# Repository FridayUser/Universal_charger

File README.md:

View this project on [CADLAB.io](https://cadlab.io/project/28066). 

# Witam w projekcie ładowarki!

# Update plików
**Proszę o pisanie jasnego podsumowania i zwięzłych opisów** przy zatwierdzaniu plików. W szczególności plików innych niż programy. Pamietajcie, że po zatwierdzeniu należy też pliki przesłać. ewentualnie dodać jakieś nowe. Jeśli ktoś nie ogarnia gita to polecam wersję desktop.
## Tworzenie plików i folderów
Starajmy się twożyć jak najbardziej przejrzyście to repozytorium, żeby się poprostu nie zgubić w tym wszystkim

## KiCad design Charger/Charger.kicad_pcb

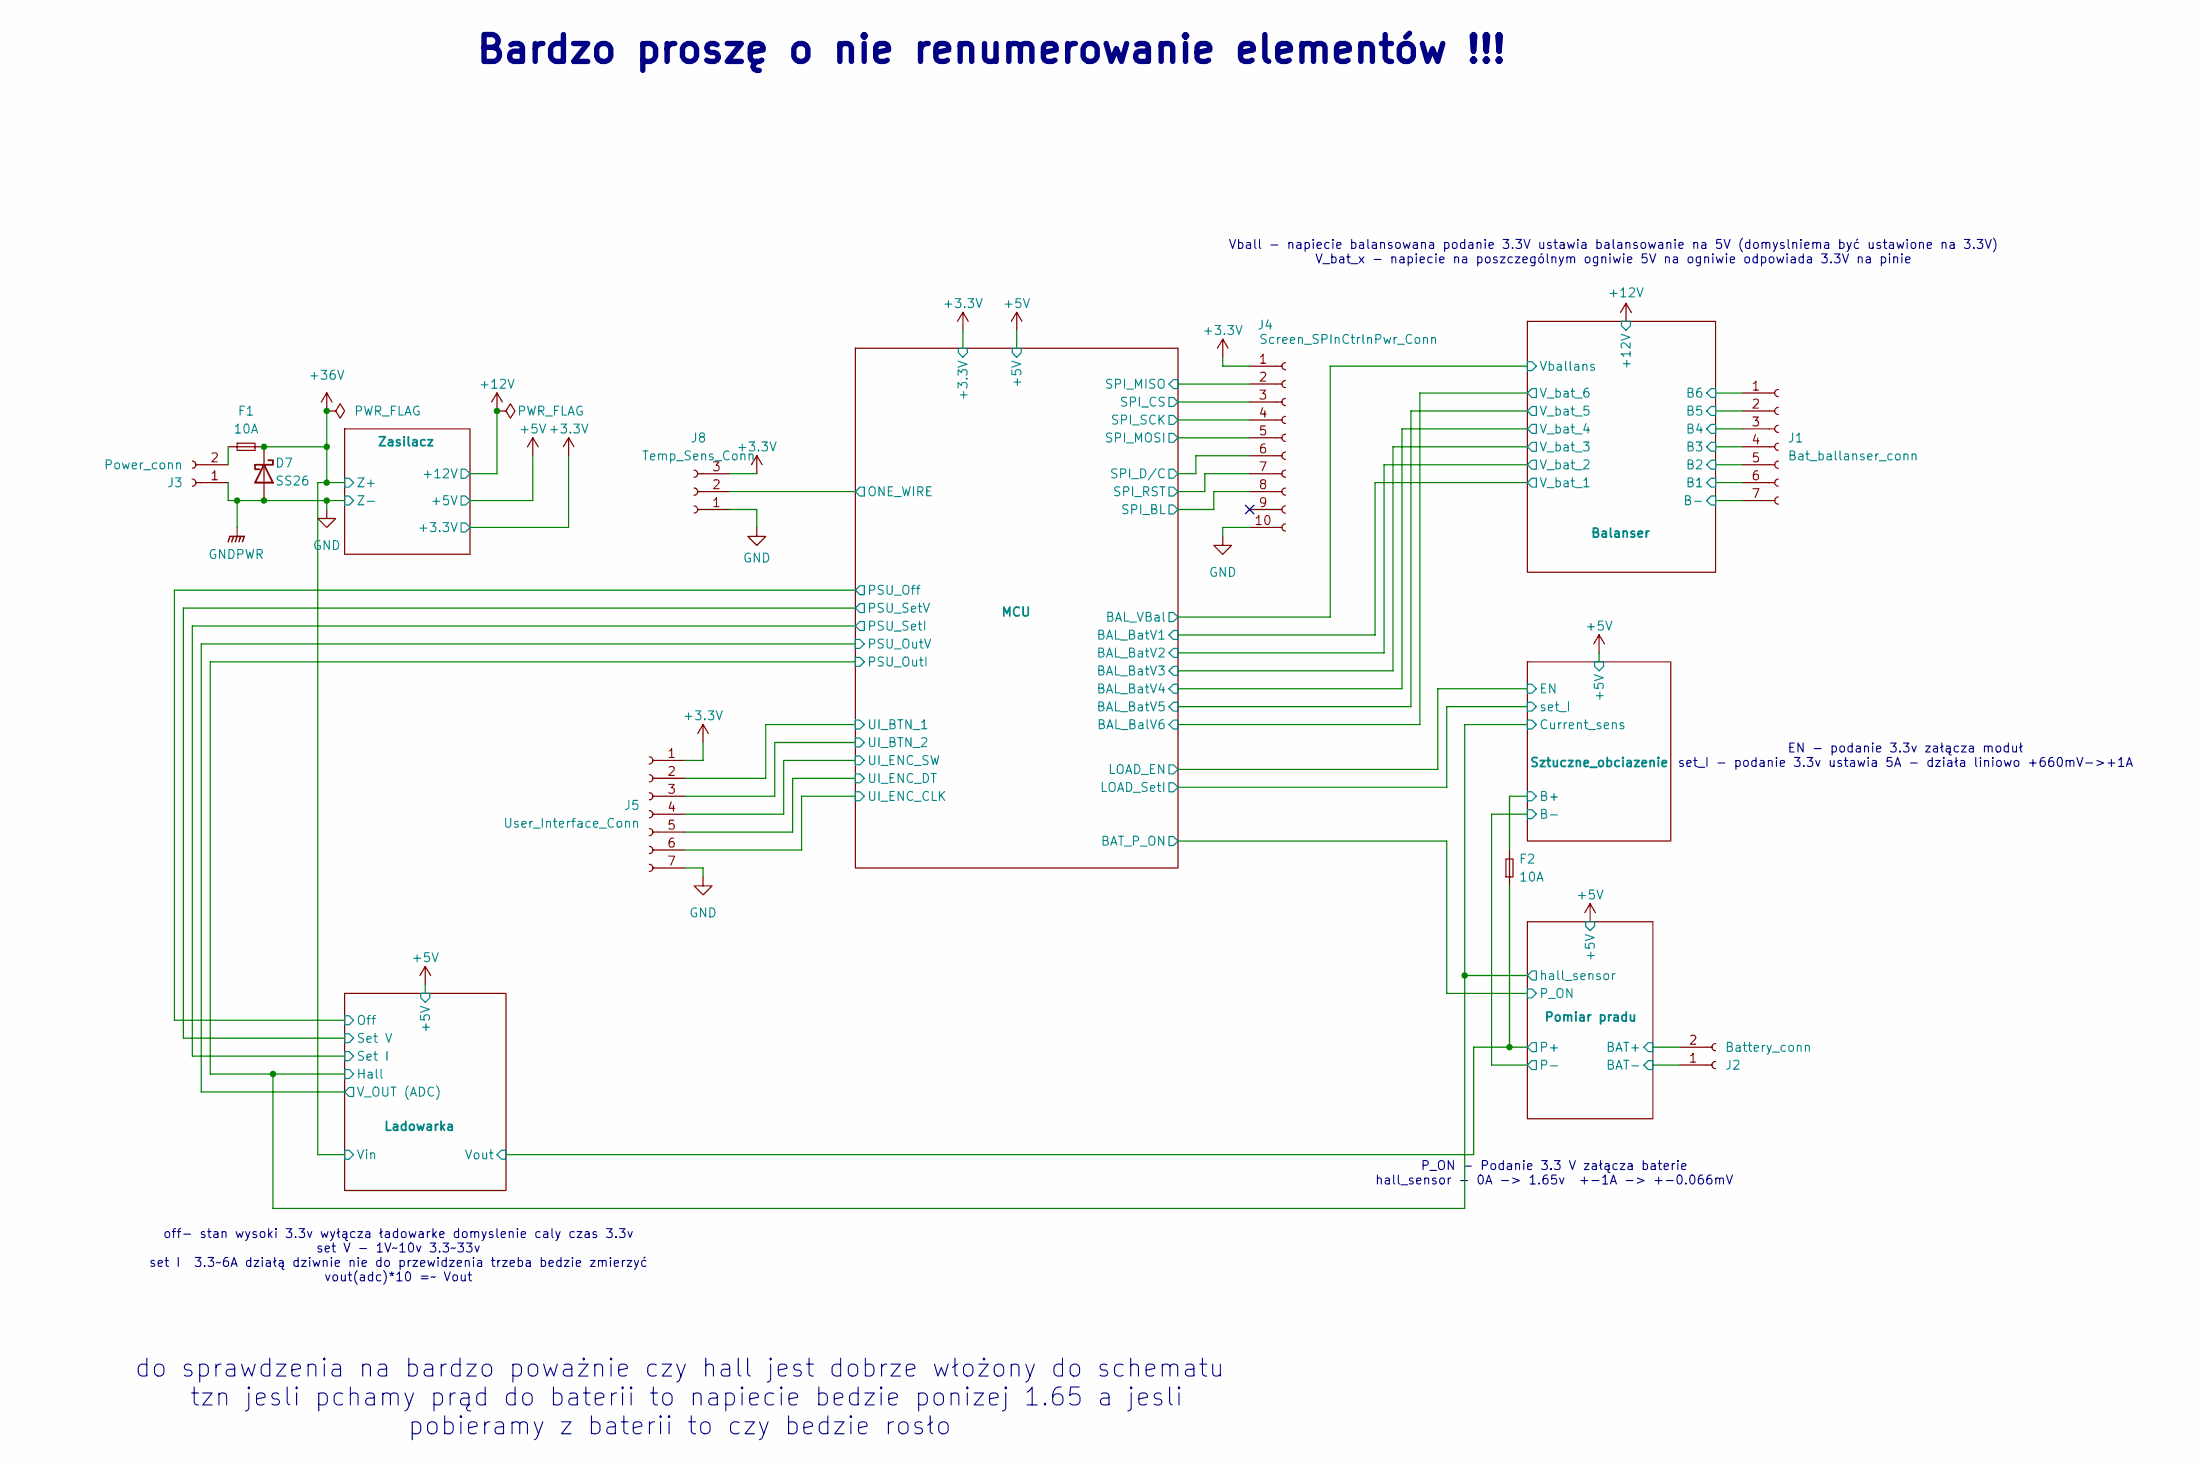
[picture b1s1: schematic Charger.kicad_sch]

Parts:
D7: SS26; D_SMA
F1, F2: 10A; Fuse_2010_5025Metric_Pad1.52x2.65mm_HandSolder
J1: Bat_ballanser_conn; PinHeader_1x07_P2.54mm_Horizontal
J2: Battery_conn; AMASS_XT60PW-M_1x02_P7.20mm_Horizontal
J3: Power_conn; AMASS_XT60PW-M_1x02_P7.20mm_Horizontal
J4: Screen_SPInCtrlnPwr_Conn; PinHeader_1x10_P2.54mm_Vertical
J5: User_Interface_Conn; PinHeader_1x07_P2.54mm_Vertical
J8: Temp_Sens_Conn; PinHeader_1x03_P2.54mm_Vertical

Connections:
+3.3V: J4.1, J5.1, J8.3; also elsewhere on the board
+36V: D7.1 (K), F1.2; also elsewhere on the board
/Balanser/B1: J1.6; also elsewhere on the board
/Balanser/B2: J1.5; also elsewhere on the board
/Balanser/B3: J1.4; also elsewhere on the board
/Balanser/B4: J1.3; also elsewhere on the board
/Balanser/B5: J1.2; also elsewhere on the board
/Balanser/B6: J1.1; also elsewhere on the board
/Ladowarka/Vout: F2.1; also elsewhere on the board
/Pomiar pradu/BAT+: J2.2; also elsewhere on the board
/Pomiar pradu/BAT-: J2.1; also elsewhere on the board
/Sztuczne_obciazenie/B+: F2.2; also elsewhere on the board
GND: D7.2 (A), J1.7, J3.1, J4.10, J5.7, J8.1; also elsewhere on the board
GPIO4: J8.2; also elsewhere on the board
GPIO11: J5.6; also elsewhere on the board
GPIO12: J5.5; also elsewhere on the board
GPIO13: J5.4; also elsewhere on the board
GPIO14: J5.3; also elsewhere on the board
GPIO15: J5.2; also elsewhere on the board
GPIO16: J4.2; also elsewhere on the board
GPIO17: J4.3; also elsewhere on the board
GPIO18: J4.4; also elsewhere on the board
GPIO19: J4.5; also elsewhere on the board
GPIO20: J4.6; also elsewhere on the board
GPIO21: J4.7; also elsewhere on the board
GPIO22: J4.8; also elsewhere on the board
unnamed: F1.1, J3.2

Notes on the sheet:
EN - podanie 3.3v załącza moduł set_I - podanie 3.3v ustawia 5A - działa liniowo +660mV->+1A
off- stan wysoki 3.3v wyłącza ładowarke domyslenie caly czas 3.3v set V - 1V~10v 3.3~33v set I 3.3~6A działą dziwnie nie do przewidzenia trzeba bedzie zmierzyć vout(adc)*10 =~ Vout
Bardzo proszę o nie renumerowanie elementów !!!
Vball - napiecie balansowana podanie 3.3V ustawia balansowanie na 5V (domyslniema być ustawione na 3.3V) V_bat_x - napiecie na poszczególnym ogniwie 5V na ogniwie odpowiada 3.3V na pinie
do sprawdzenia na bardzo poważnie czy hall jest dobrze włożony do schematu tzn jesli pchamy prąd do baterii to napiecie bedzie ponizej 1.65 a jesli pobieramy z baterii to czy bedzie rosło
P_ON - Podanie 3.3 V załącza baterie hall_sensor - 0A -> 1.65v +-1A -> +-0.066mV

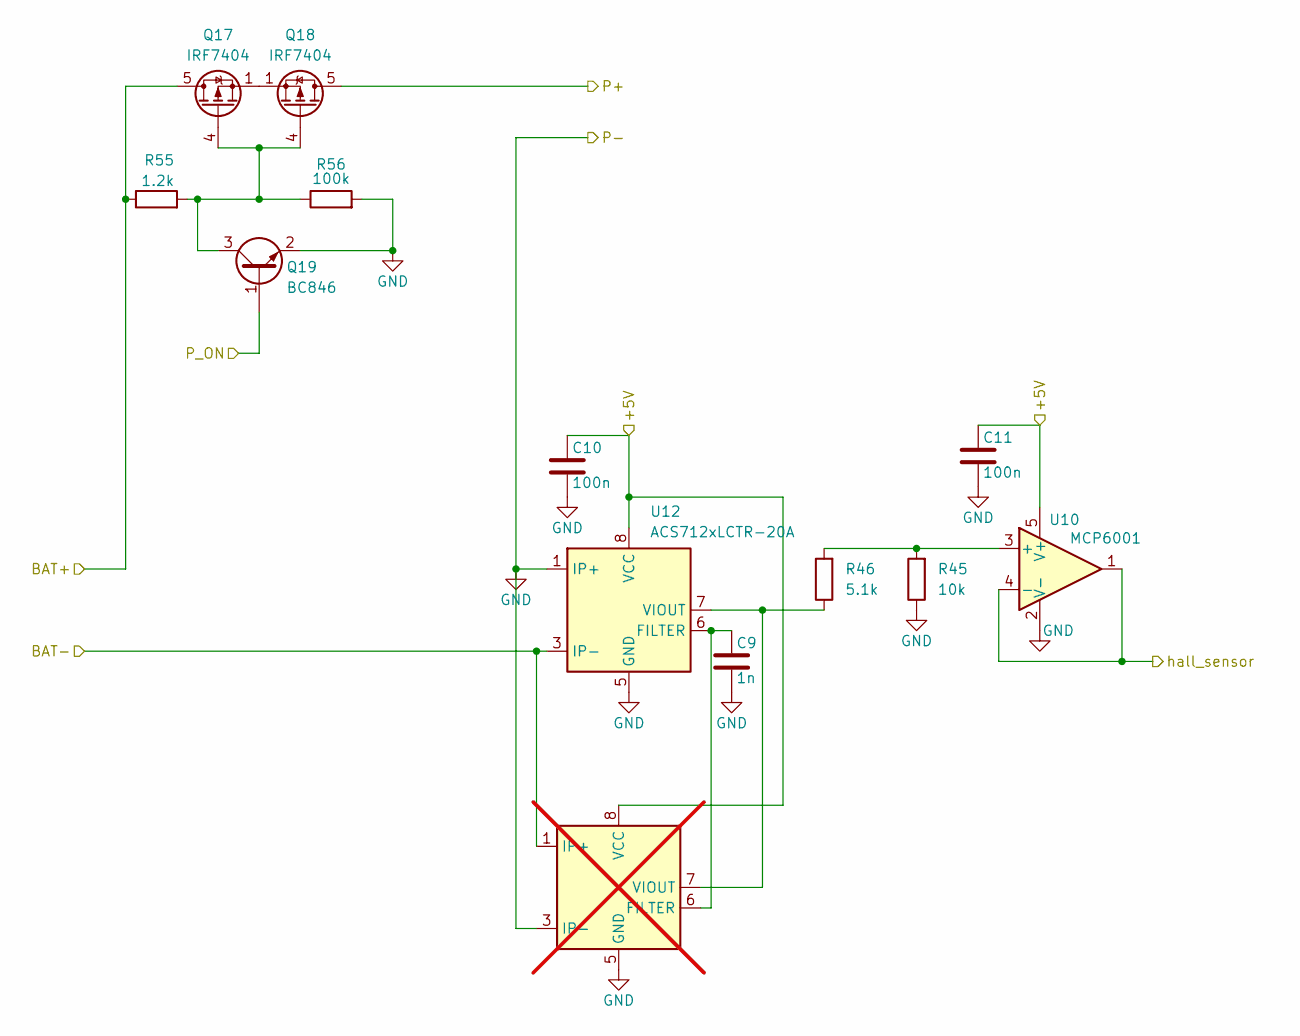
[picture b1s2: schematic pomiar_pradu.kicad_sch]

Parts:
C9: 1n; C_0805_2012Metric_Pad1.18x1.45mm_HandSolder
C10, C11: 100n; C_0805_2012Metric_Pad1.18x1.45mm_HandSolder
Q17, Q18: IRF7404; SOIC-8_3.9x4.9mm_P1.27mm
Q19: BC846; SOT-323_SC-70
R45: 10k; R_0805_2012Metric_Pad1.20x1.40mm_HandSolder
R46: 5.1k; R_0805_2012Metric_Pad1.20x1.40mm_HandSolder
R55: 1.2k; R_0805_2012Metric_Pad1.20x1.40mm_HandSolder
R56: 100k; R_0805_2012Metric_Pad1.20x1.40mm_HandSolder
U7: ACS712xLCTR-20A; SOIC-8_3.9x4.9mm_P1.27mm; not fitted
U10: MCP6001; SOT-23-5
U12: ACS712xLCTR-20A; SOIC-8_3.9x4.9mm_P1.27mm

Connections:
+5V: C10.1, C11.1, U7.8 (VCC), U10.5 (V+), U12.8 (VCC); also elsewhere on the board
/Ladowarka/Hall: U10.1, U10.4 (-); also elsewhere on the board
/Ladowarka/Vout: Q18.5 (D), Q18.6 (D), Q18.7 (D), Q18.8 (D); also elsewhere on the board
/Pomiar pradu/BAT+: Q17.5 (D), Q17.6 (D), Q17.7 (D), Q17.8 (D), R55.1; also elsewhere on the board
/Pomiar pradu/BAT-: U7.1 (IP+), U7.2 (IP+), U12.3 (IP-), U12.4 (IP-); also elsewhere on the board
GND: C9.2, C10.2, C11.2, Q19.2 (E), R45.1, R56.2, U7.3 (IP-), U7.4 (IP-), U7.5 (GND), U10.2 (V-), U12.1 (IP+), U12.2 (IP+), U12.5 (GND); also elsewhere on the board
GPIO10: Q19.1 (B); also elsewhere on the board
unnamed: Q17.4 (G), Q18.4 (G), Q19.3 (C), R55.2, R56.1
unnamed: Q17.1 (S), Q17.2 (S), Q17.3 (S), Q18.1 (S), Q18.2 (S), Q18.3 (S)
unnamed: R45.2, R46.2, U10.3 (+)
unnamed: C9.1, U7.6 (FILTER), U12.6 (FILTER)
unnamed 106: R46.1, U7.7 (VIOUT), U12.7 (VIOUT); also elsewhere on the board

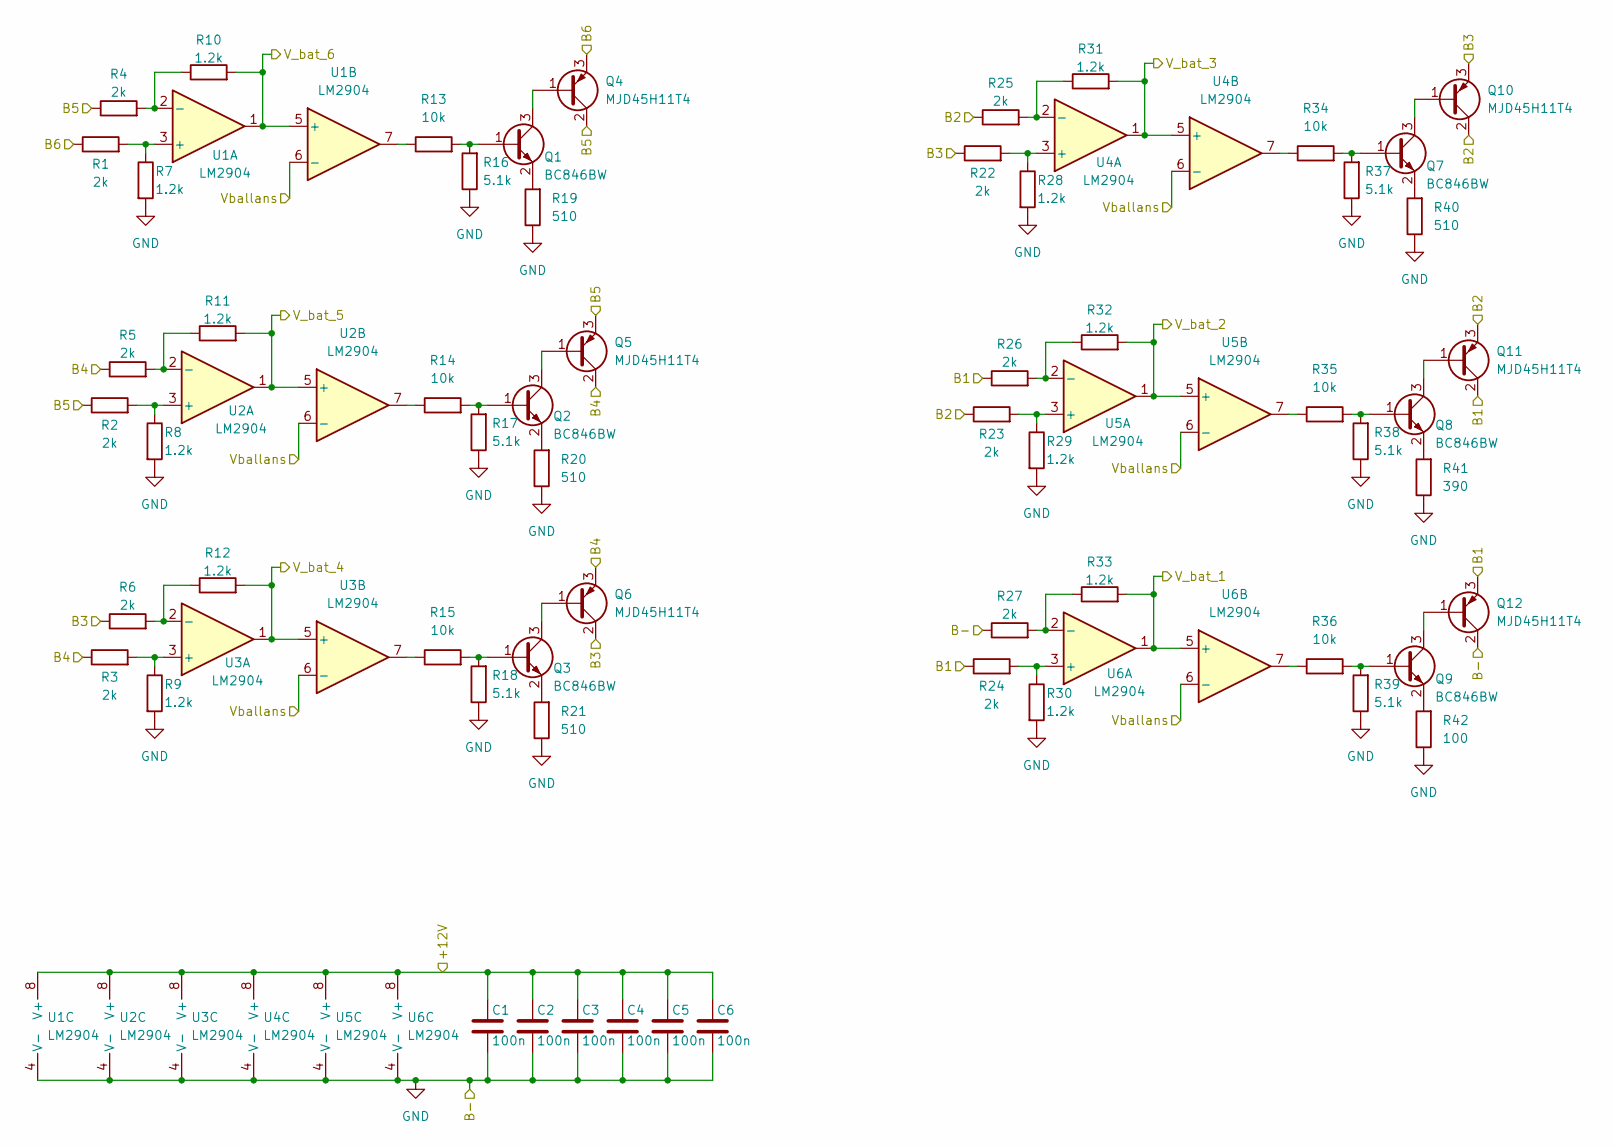
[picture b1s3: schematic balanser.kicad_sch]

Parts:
C1, C2, C3, C4, C5, C6: 100n; C_0805_2012Metric_Pad1.18x1.45mm_HandSolder
Q1, Q2, Q3, Q7, Q8, Q9: BC846BW; SOT-323_SC-70
Q4, Q5, Q6, Q10, Q11, Q12: MJD45H11T4; TO-252-2
R1, R2, R3, R4, R5, R6, R22, R23, R24, R25, R26, R27: 2k; R_0805_2012Metric_Pad1.20x1.40mm_HandSolder
R7, R8, R9, R10, R11, R12, R28, R29, R30, R31, R32, R33: 1.2k; R_0805_2012Metric_Pad1.20x1.40mm_HandSolder
R13, R14, R15, R34, R35, R36: 10k; R_0805_2012Metric_Pad1.20x1.40mm_HandSolder
R16, R17, R18, R37, R38, R39: 5.1k; R_0805_2012Metric_Pad1.20x1.40mm_HandSolder
R19, R20, R21, R40: 510; R_0805_2012Metric_Pad1.20x1.40mm_HandSolder
R41: 390; R_0805_2012Metric_Pad1.20x1.40mm_HandSolder
R42: 100; R_0805_2012Metric_Pad1.20x1.40mm_HandSolder
U1, U2, U3, U4, U5, U6: LM2904; SO-8_3.9x4.9mm_P1.27mm

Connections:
+12V: C1.1, C2.1, C3.1, C4.1, C5.1, C6.1, U1.8 (V+), U2.8 (V+), U3.8 (V+), U4.8 (V+), U5.8 (V+), U6.8 (V+); also elsewhere on the board
/Balanser/B1: Q11.2 (C), Q12.3 (E), R24.1, R26.1; also elsewhere on the board
/Balanser/B2: Q10.2 (C), Q11.3 (E), R23.1, R25.1; also elsewhere on the board
/Balanser/B3: Q6.2 (C), Q10.3 (E), R6.1, R22.1; also elsewhere on the board
/Balanser/B4: Q5.2 (C), Q6.3 (E), R3.1, R5.1; also elsewhere on the board
/Balanser/B5: Q4.2 (C), Q5.3 (E), R2.1, R4.1; also elsewhere on the board
/Balanser/B6: Q4.3 (E), R1.1; also elsewhere on the board
/Balanser/V_bat_1: R33.2, U6.1, U6.5 (+); also elsewhere on the board
/Balanser/V_bat_2: R32.2, U5.1, U5.5 (+); also elsewhere on the board
/Balanser/V_bat_3: R31.2, U4.1, U4.5 (+); also elsewhere on the board
/Balanser/V_bat_4: R12.2, U3.1, U3.5 (+); also elsewhere on the board
/Balanser/V_bat_5: R11.2, U2.1, U2.5 (+); also elsewhere on the board
/Balanser/V_bat_6: R10.2, U1.1, U1.5 (+); also elsewhere on the board
/Balanser/Vballans: U1.6 (-), U2.6 (-), U3.6 (-), U4.6 (-), U5.6 (-), U6.6 (-); also elsewhere on the board
GND: C1.2, C2.2, C3.2, C4.2, C5.2, C6.2, Q12.2 (C), R7.2, R8.2, R9.2, R16.1, R17.1, R18.1, R19.1, R20.1, R21.1, R27.1, R28.2, R29.2, R30.2, R37.1, R38.1, R39.1, R40.1, R41.1, R42.1, U1.4 (V-), U2.4 (V-), U3.4 (V-), U4.4 (V-), U5.4 (V-), U6.4 (V-); also elsewhere on the board
unnamed: Q1.1 (B), R13.2, R16.2
unnamed: Q1.3 (C), Q4.1 (B)
unnamed: Q1.2 (E), R19.2
unnamed: Q2.1 (B), R14.2, R17.2
unnamed: Q2.3 (C), Q5.1 (B)
unnamed: Q2.2 (E), R20.2
unnamed: Q3.1 (B), R15.2, R18.2
unnamed: Q3.3 (C), Q6.1 (B)
unnamed: Q3.2 (E), R21.2
unnamed: Q7.1 (B), R34.2, R37.2
unnamed: Q7.2 (E), R40.2
unnamed: Q8.1 (B), R35.2, R38.2
unnamed: Q8.2 (E), R41.2
unnamed: Q9.1 (B), R36.2, R39.2
unnamed: Q9.2 (E), R42.2
unnamed: Q7.3 (C), Q10.1 (B)
unnamed: Q8.3 (C), Q11.1 (B)
unnamed: Q9.3 (C), Q12.1 (B)
unnamed: R13.1, U1.7
unnamed: R14.1, U2.7
unnamed: R15.1, U3.7
unnamed: R34.1, U4.7
unnamed: R35.1, U5.7
unnamed: R36.1, U6.7
unnamed: R1.2, R7.1, U1.3 (+)
unnamed: R4.2, R10.1, U1.2 (-)
unnamed: R2.2, R8.1, U2.3 (+)
unnamed: R5.2, R11.1, U2.2 (-)
unnamed: R3.2, R9.1, U3.3 (+)
unnamed: R6.2, R12.1, U3.2 (-)
unnamed: R22.2, R28.1, U4.3 (+)
unnamed: R25.2, R31.1, U4.2 (-)
unnamed: R23.2, R29.1, U5.3 (+)
unnamed: R26.2, R32.1, U5.2 (-)
unnamed: R24.2, R30.1, U6.3 (+)
unnamed: R27.2, R33.1, U6.2 (-)

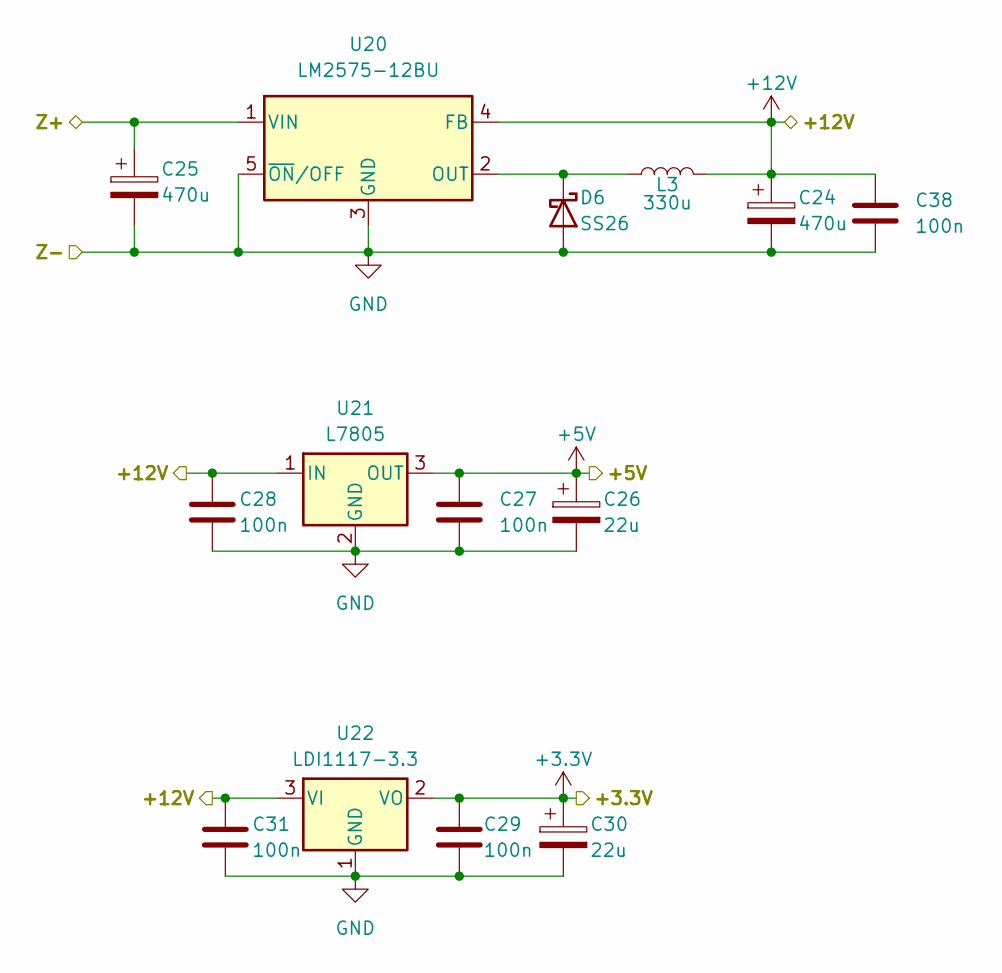
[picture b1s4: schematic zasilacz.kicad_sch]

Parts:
C24, C25: 470u; CP_Elec_12.5x13.5
C26, C30: 22u; CP_Elec_4x5.4
C27, C28, C29, C31, C38: 100n; C_0805_2012Metric_Pad1.18x1.45mm_HandSolder
D6: SS26; D_SMA
L3: 330u; L_Bourns_SRR1208_12.7x12.7mm
U20: LM2575-12BU; TO-263-5_TabPin3
U21: L7805; TO-263-2
U22: LDI1117-3.3; SOT-223-3_TabPin2

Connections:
+3.3V: C29.1, C30.1, U22.2 (VO); also elsewhere on the board
+5V: C26.1, C27.1, U21.3 (OUT); also elsewhere on the board
+12V: C24.1, C28.1, C31.1, C38.1, L3.2, U20.4 (FB), U21.1 (IN), U22.3 (VI); also elsewhere on the board
+36V: C25.1, U20.1 (VIN); also elsewhere on the board
GND: C24.2, C25.2, C26.2, C27.2, C28.2, C29.2, C30.2, C31.2, C38.2, D6.2 (A), U20.3 (GND), U20.5 (~ON/OFF), U21.2 (GND), U22.1 (GND); also elsewhere on the board
unnamed: D6.1 (K), L3.1, U20.2 (OUT)

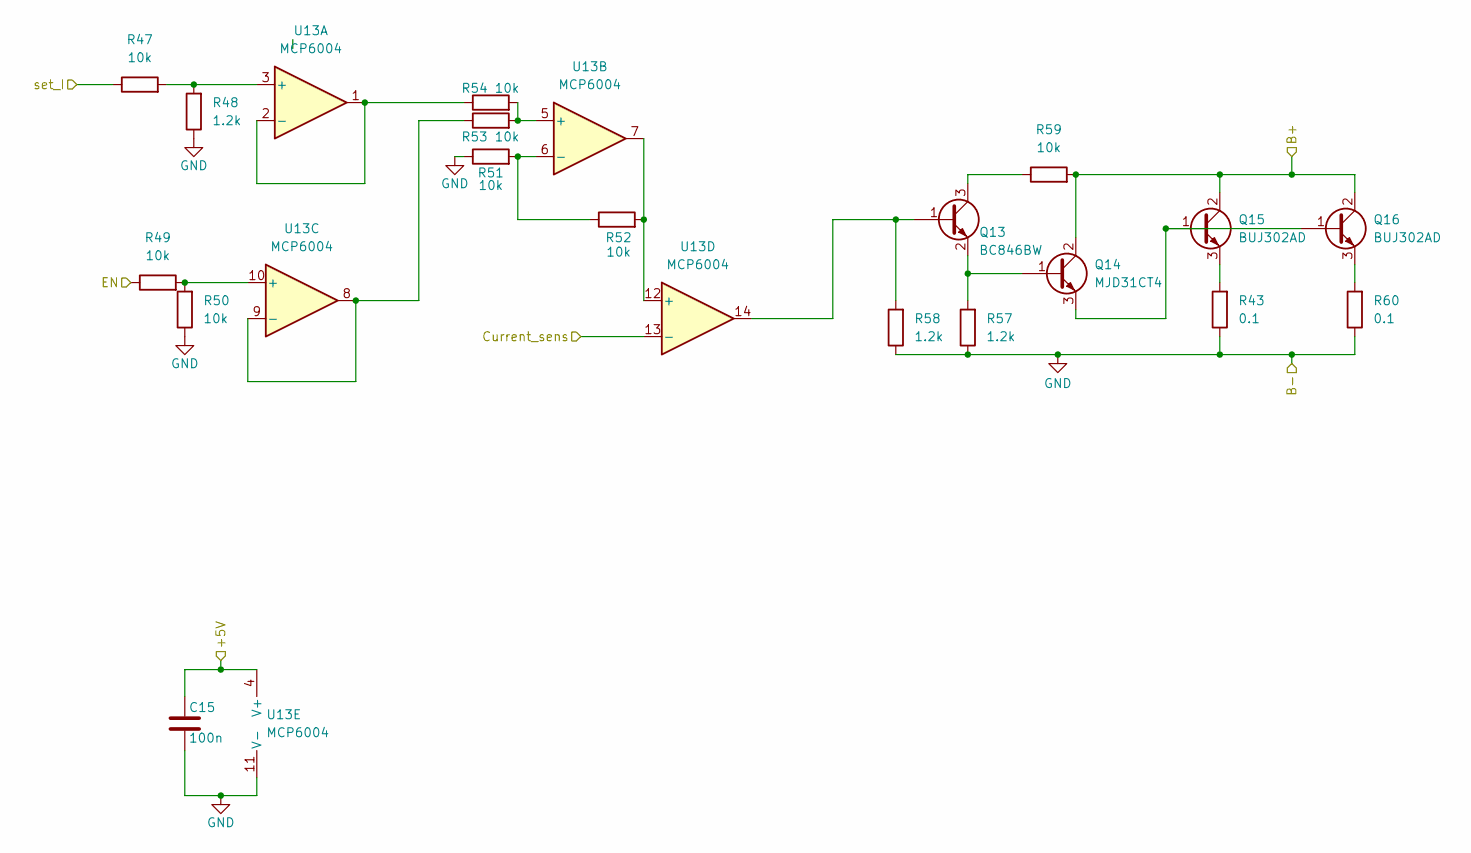
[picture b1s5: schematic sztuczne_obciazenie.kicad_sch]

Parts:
C15: 100n; C_0805_2012Metric_Pad1.18x1.45mm_HandSolder
Q13: BC846BW; SOT-323_SC-70
Q14: MJD31CT4; TO-252-2
Q15, Q16: BUJ302AD; TO-252-2
R43, R60: 0.1; R_1206_3216Metric_Pad1.30x1.75mm_HandSolder
R47, R49, R50, R51, R52, R53, R54, R59: 10k; R_0805_2012Metric_Pad1.20x1.40mm_HandSolder
R48, R57, R58: 1.2k; R_0805_2012Metric_Pad1.20x1.40mm_HandSolder
U13: MCP6004; SOIC-14_3.9x8.7mm_P1.27mm

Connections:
+5V: C15.1, U13.4 (V+); also elsewhere on the board
/Ladowarka/Hall: U13.13 (-); also elsewhere on the board
/MCU/LOAD_SetI: R47.1; also elsewhere on the board
/Sztuczne_obciazenie/B+: Q14.2 (C), Q15.2 (C), Q16.2 (C), R59.2; also elsewhere on the board
GND: C15.2, R43.1, R48.1, R50.1, R51.1, R57.1, R58.1, R60.1, U13.11 (V-); also elsewhere on the board
GPIO8: R49.1; also elsewhere on the board
unnamed: Q13.1 (B), R58.2, U13.14
unnamed: Q13.3 (C), R59.1
unnamed: Q13.2 (E), Q14.1 (B), R57.2
unnamed: Q14.3 (E), Q15.1 (B), Q16.1 (B)
unnamed: Q15.3 (E), R43.2
unnamed: Q16.3 (E), R60.2
unnamed: R47.2, R48.2, U13.3 (+)
unnamed: R54.1, U13.1, U13.2 (-)
unnamed: R53.2, R54.2, U13.5 (+)
unnamed: R51.2, R52.1, U13.6 (-)
unnamed: R49.2, R50.2, U13.10 (+)
unnamed: R53.1, U13.8, U13.9 (-)
unnamed: R52.2, U13.7, U13.12 (+)

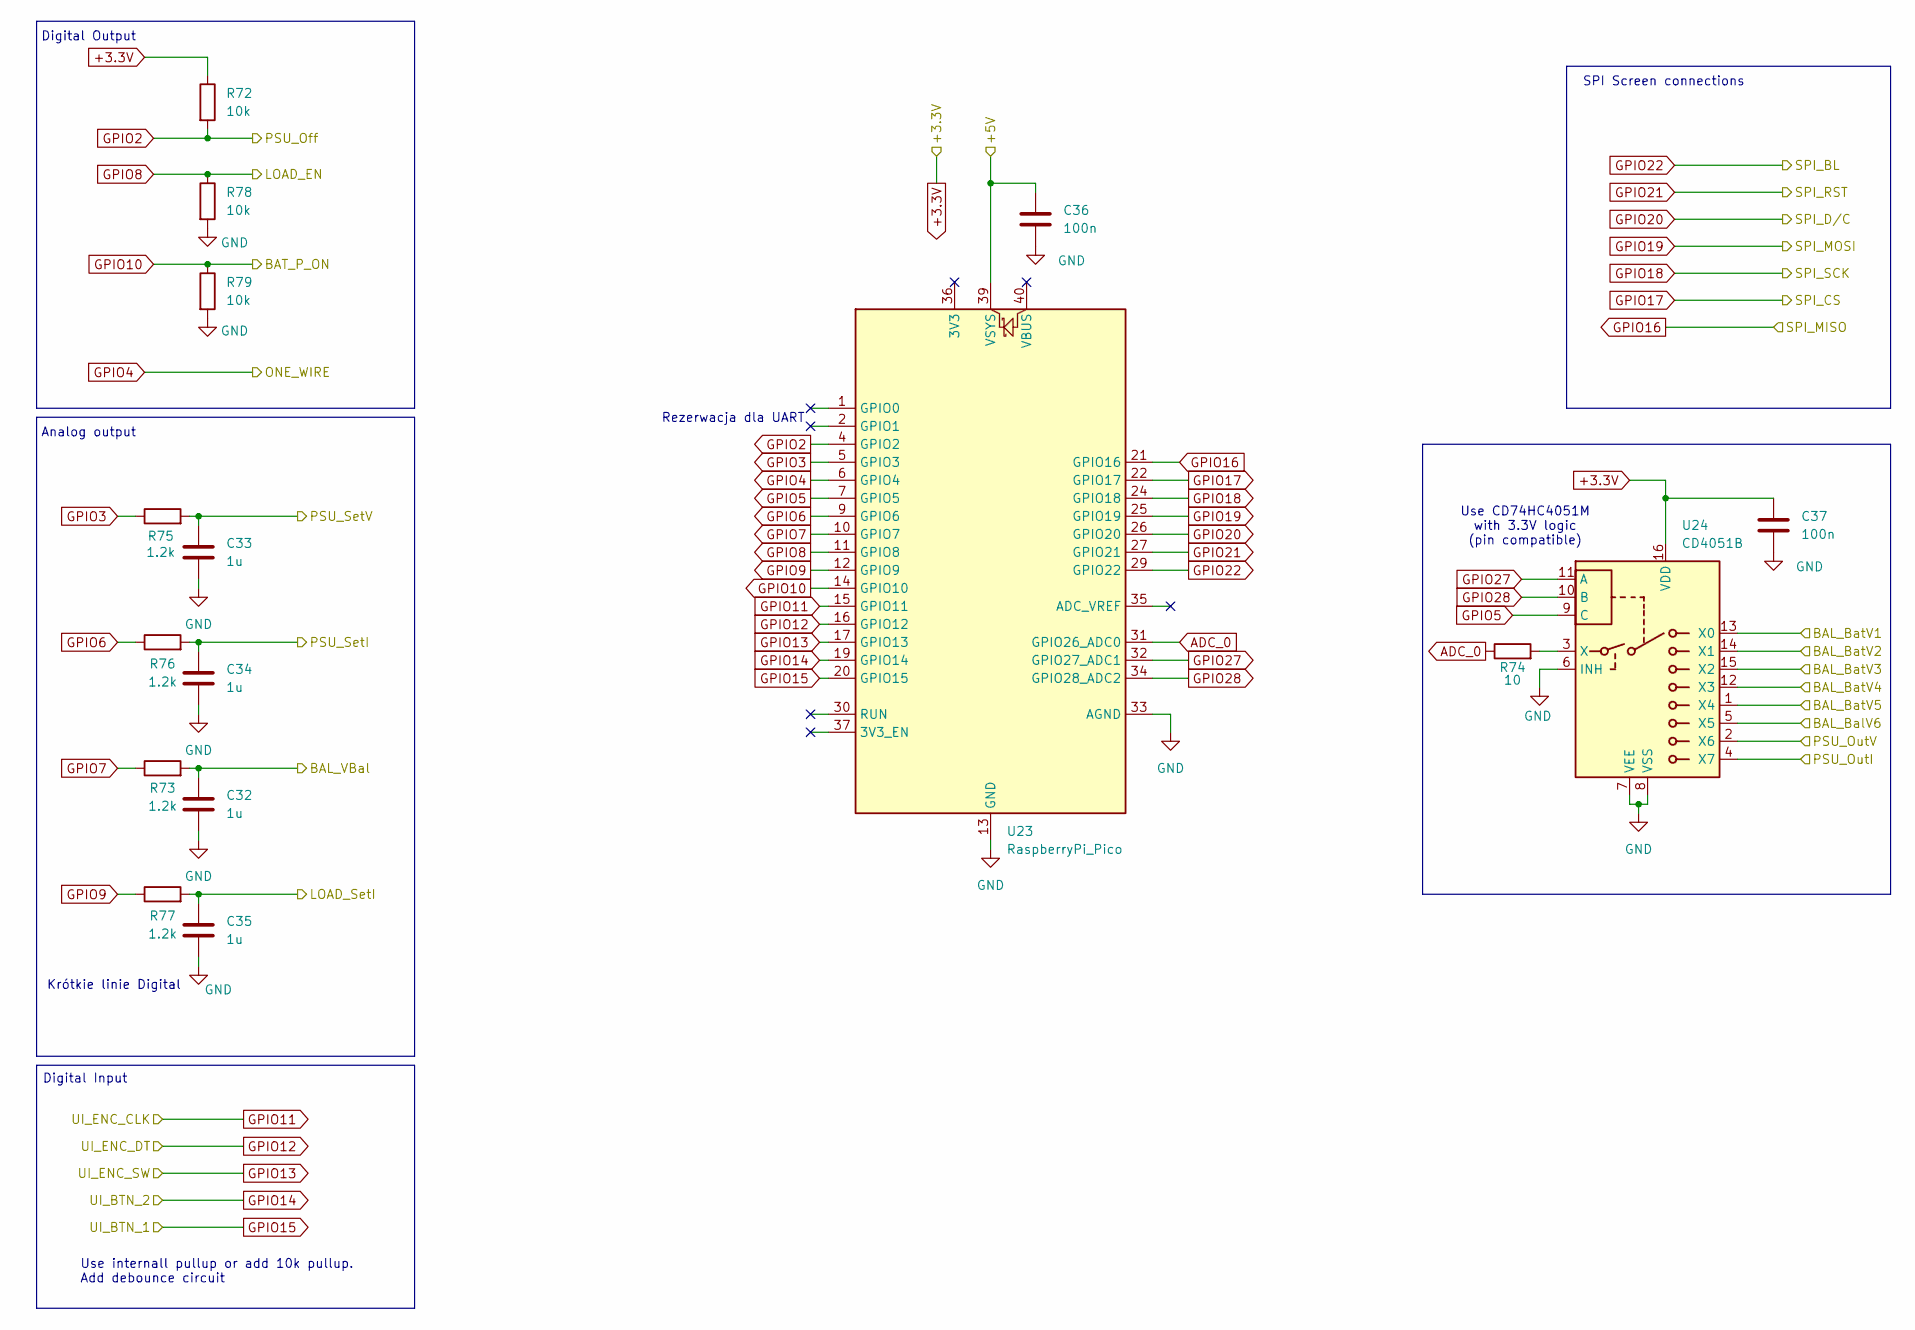
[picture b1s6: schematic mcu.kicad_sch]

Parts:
C32, C33, C34, C35: 1u; C_0805_2012Metric_Pad1.18x1.45mm_HandSolder
C36, C37: 100n; C_0805_2012Metric_Pad1.18x1.45mm_HandSolder
R72, R78, R79: 10k; R_0805_2012Metric_Pad1.20x1.40mm_HandSolder
R73, R75, R76, R77: 1.2k; R_0805_2012Metric_Pad1.20x1.40mm_HandSolder
R74: 10; R_0805_2012Metric_Pad1.20x1.40mm_HandSolder
U23: RaspberryPi_Pico; RaspberryPi_Pico_Common_SMD
U24: CD4051B; SO-16_5.3x10.2mm_P1.27mm

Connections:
+3.3V: C37.1, R72.1, U24.16 (VDD); also elsewhere on the board
+5V: C36.1, U23.39 (VSYS); also elsewhere on the board
/Balanser/V_bat_1: U24.13 (X0); also elsewhere on the board
/Balanser/V_bat_2: U24.14 (X1); also elsewhere on the board
/Balanser/V_bat_3: U24.15 (X2); also elsewhere on the board
/Balanser/V_bat_4: U24.12 (X3); also elsewhere on the board
/Balanser/V_bat_5: U24.1 (X4); also elsewhere on the board
/Balanser/V_bat_6: U24.5 (X5); also elsewhere on the board
/Balanser/Vballans: C32.1, R73.2; also elsewhere on the board
/Ladowarka/Hall: U24.4 (X7); also elsewhere on the board
/Ladowarka/Set I: C34.1, R76.2; also elsewhere on the board
/Ladowarka/Set V: C33.1, R75.2; also elsewhere on the board
/Ladowarka/V_OUT (ADC): U24.2 (X6); also elsewhere on the board
/MCU/LOAD_SetI: C35.1, R77.2; also elsewhere on the board
ADC_0: R74.1, U23.31 (GPIO26_ADC0); also elsewhere on the board
GND: C32.2, C33.2, C34.2, C35.2, C36.2, C37.2, R78.2, R79.2, U23.3 (GND), U23.8 (GND), U23.13 (GND), U23.18 (GND), U23.23 (GND), U23.28 (GND), U23.33 (AGND), U23.38 (GND), U24.6 (INH), U24.7 (VEE), U24.8 (VSS); also elsewhere on the board
GPIO2: R72.2, U23.4 (GPIO2); also elsewhere on the board
GPIO3: R75.1, U23.5 (GPIO3)
GPIO4: U23.6 (GPIO4); also elsewhere on the board
GPIO5: U23.7 (GPIO5), U24.9 (C)
GPIO6: R76.1, U23.9 (GPIO6)
GPIO7: R73.1, U23.10 (GPIO7)
GPIO8: R78.1, U23.11 (GPIO8); also elsewhere on the board
GPIO9: R77.1, U23.12 (GPIO9)
GPIO10: R79.1, U23.14 (GPIO10); also elsewhere on the board
GPIO11: U23.15 (GPIO11); also elsewhere on the board
GPIO12: U23.16 (GPIO12); also elsewhere on the board
GPIO13: U23.17 (GPIO13); also elsewhere on the board
GPIO14: U23.19 (GPIO14); also elsewhere on the board
GPIO15: U23.20 (GPIO15); also elsewhere on the board
GPIO16: U23.21 (GPIO16); also elsewhere on the board
GPIO17: U23.22 (GPIO17); also elsewhere on the board
GPIO18: U23.24 (GPIO18); also elsewhere on the board
GPIO19: U23.25 (GPIO19); also elsewhere on the board
GPIO20: U23.26 (GPIO20); also elsewhere on the board
GPIO21: U23.27 (GPIO21); also elsewhere on the board
GPIO22: U23.29 (GPIO22); also elsewhere on the board
GPIO27: U23.32 (GPIO27_ADC1), U24.11 (A)
GPIO28: U23.34 (GPIO28_ADC2), U24.10 (B)
unnamed: R74.2, U24.3 (X)

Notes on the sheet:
Rezerwacja dla UART
Analog output
Digital Output
SPI Screen connections
Krótkie linie Digital
Use CD74HC4051M with 3.3V logic (pin compatible)
Use internall pullup or add 10k pullup. Add debounce circuit
Digital Input

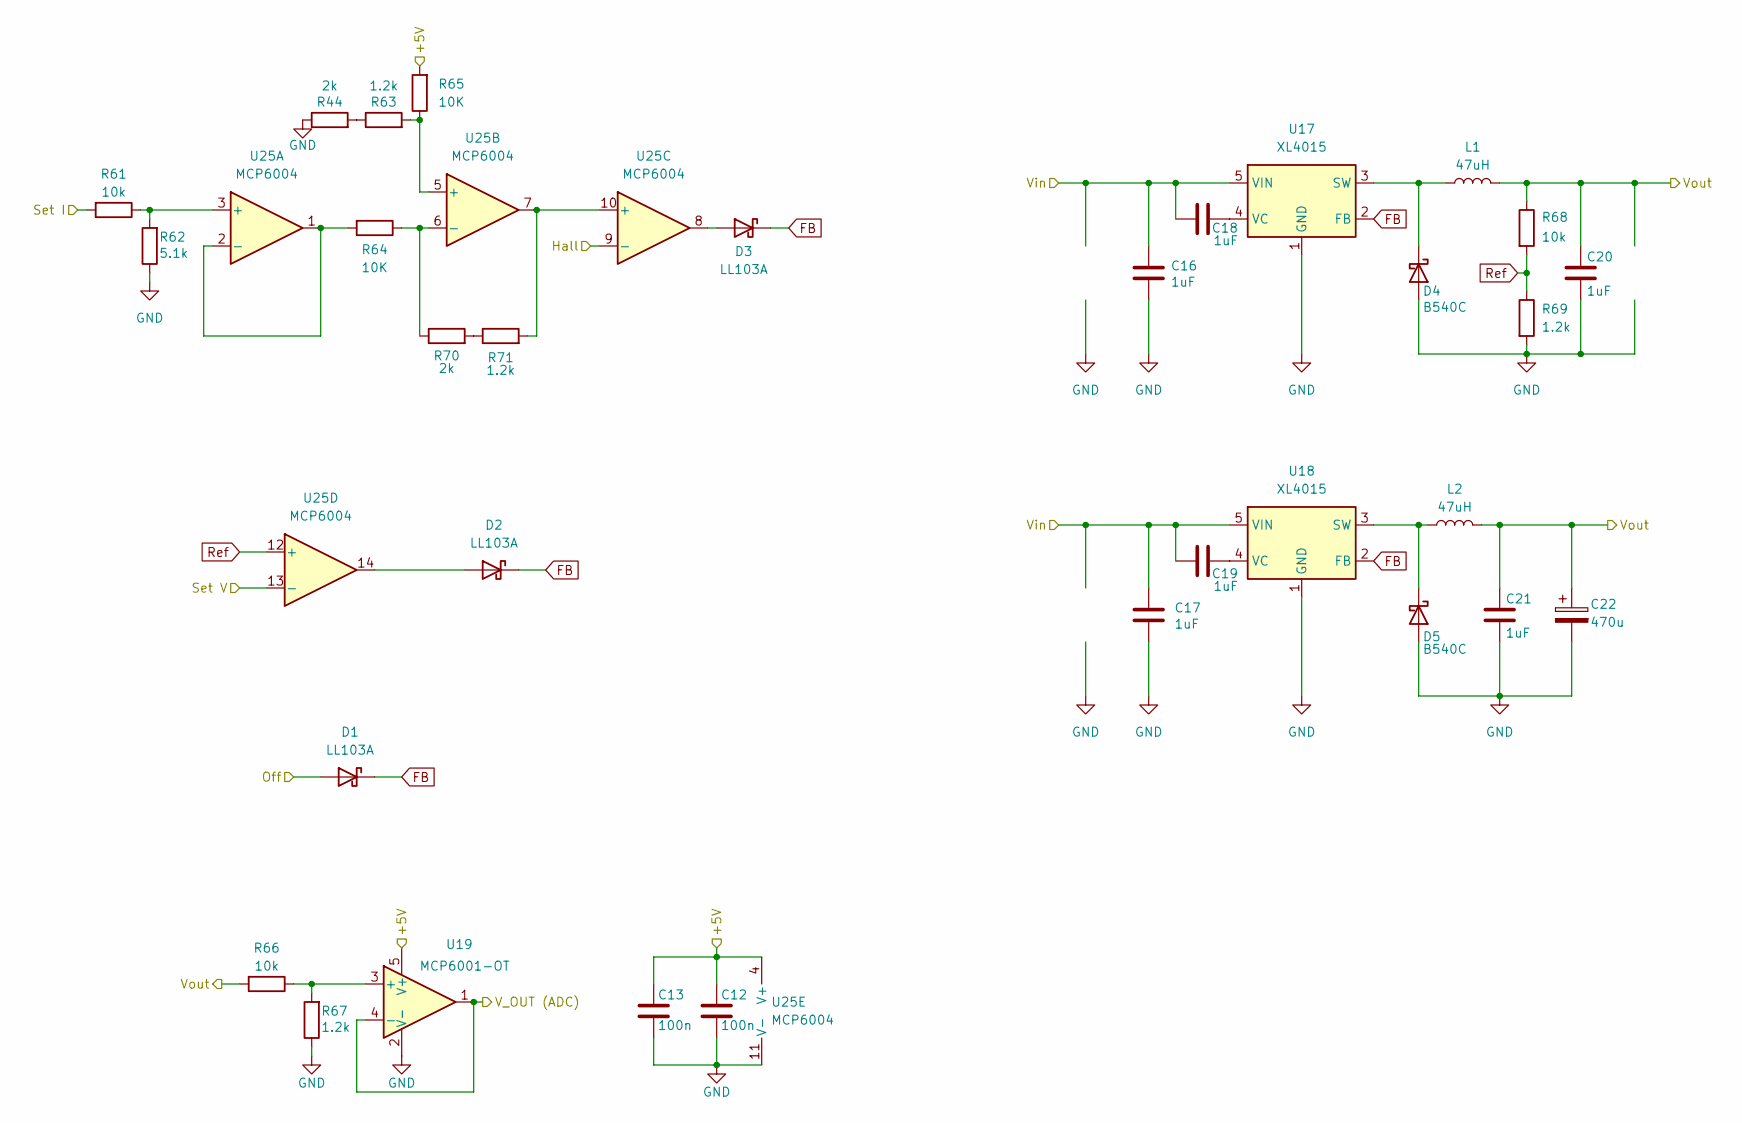
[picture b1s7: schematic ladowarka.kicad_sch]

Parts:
C12, C13: 100n; C_0805_2012Metric_Pad1.18x1.45mm_HandSolder
C16, C17, C18, C19, C20, C21: 1uF; C_0805_2012Metric_Pad1.18x1.45mm_HandSolder
C22: 470u; CP_Elec_12.5x13.5
D1, D2, D3: LL103A; D_MiniMELF
D4, D5: B540C; D_3220_8050Metric_Pad2.65x5.15mm_HandSolder
L1, L2: 47uH; L_Bourns_SRP1038C_10.0x10.0mm
R44, R70: 2k; R_0805_2012Metric_Pad1.20x1.40mm_HandSolder
R61, R66, R68: 10k; R_0805_2012Metric_Pad1.20x1.40mm_HandSolder
R62: 5.1k; R_0805_2012Metric_Pad1.20x1.40mm_HandSolder
R63, R67, R69, R71: 1.2k; R_0805_2012Metric_Pad1.20x1.40mm_HandSolder
R64, R65: 10K; R_0805_2012Metric_Pad1.20x1.40mm_HandSolder
U17, U18: XL4015; TO-263-5_TabPin3
U19: MCP6001-OT; SOT-23-5
U25: MCP6004; SOIC-14_3.9x8.7mm_P1.27mm

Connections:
+5V: C12.1, C13.1, R65.2, U19.5 (V+), U25.4 (V+); also elsewhere on the board
+36V: C16.1, C17.1, C18.1, C19.1, U17.5 (VIN), U18.5 (VIN); also elsewhere on the board
/Ladowarka/Hall: U25.9 (-); also elsewhere on the board
/Ladowarka/Set I: R61.2; also elsewhere on the board
/Ladowarka/Set V: U25.13 (-); also elsewhere on the board
/Ladowarka/V_OUT (ADC): U19.1, U19.4 (-); also elsewhere on the board
/Ladowarka/Vout: C20.1, C21.1, C22.1, L1.2, L2.2, R66.2, R68.1; also elsewhere on the board
FB: D1.1 (K), D2.1 (K), D3.1 (K), U17.2 (FB), U18.2 (FB)
GND: C12.2, C13.2, C16.2, C17.2, C20.2, C21.2, C22.2, D4.2 (A), D5.2 (A), R44.1, R62.1, R67.1, R69.2, U17.1 (GND), U18.1 (GND), U19.2 (V-), U25.11 (V-); also elsewhere on the board
GPIO2: D1.2 (A); also elsewhere on the board
unnamed: D2.2 (A), U25.14
unnamed: D3.2 (A), U25.8
unnamed: D4.1 (K), L1.1, U17.3 (SW)
unnamed: D5.1 (K), L2.1, U18.3 (SW)
unnamed: R44.2, R63.1
unnamed: R70.2, R71.1
unnamed: C18.2, U17.4 (VC)
unnamed: C19.2, U18.4 (VC)
unnamed: R66.1, R67.2, U19.3 (+)
unnamed: R61.1, R62.2, U25.3 (+)
unnamed: R64.2, U25.1, U25.2 (-)
unnamed: R63.2, R65.1, U25.5 (+)
unnamed: R64.1, R70.1, U25.6 (-)
unnamed: R71.2, U25.7, U25.10 (+)
Ref: R68.2, R69.1, U25.12 (+)
